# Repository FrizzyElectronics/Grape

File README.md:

# Grape

Grape es un Arduino&trade; compatible de fabricacion y diseño español. Destaca frente a otras placas por su rapidez de conexionado y por no necesitar el uso de protoboard para realizar los proyectos.

## Rasgos destacados

  - Conexion micro-USB
  - Corriente max de salida (5V) 2A
  - Pines de conexión rápida
  - Interruptor de encendido-apagado
  - 8 pines analogicos
  - Compatible con los shields de Arduino&trade; y con Arduino&trade; IDE

## Documentacion 

* **/Hardware** - Archivos de diseño en KiCad e Eagle, esquema en PDF
* **/Production** - Gerbers, BOM
* **/Design** - Logos, SVG 

Licencia
-------------------

Este producto es  **open source**! 

Por favor, revisa el archivo [LICENSE.md](https://github.com/FrizzyElectronics/Grape/blob/master/License.md) para más información. 

Si tiene alguna duda acerca del uso de esta licencia contatanos a traves de  info@frizzy.es

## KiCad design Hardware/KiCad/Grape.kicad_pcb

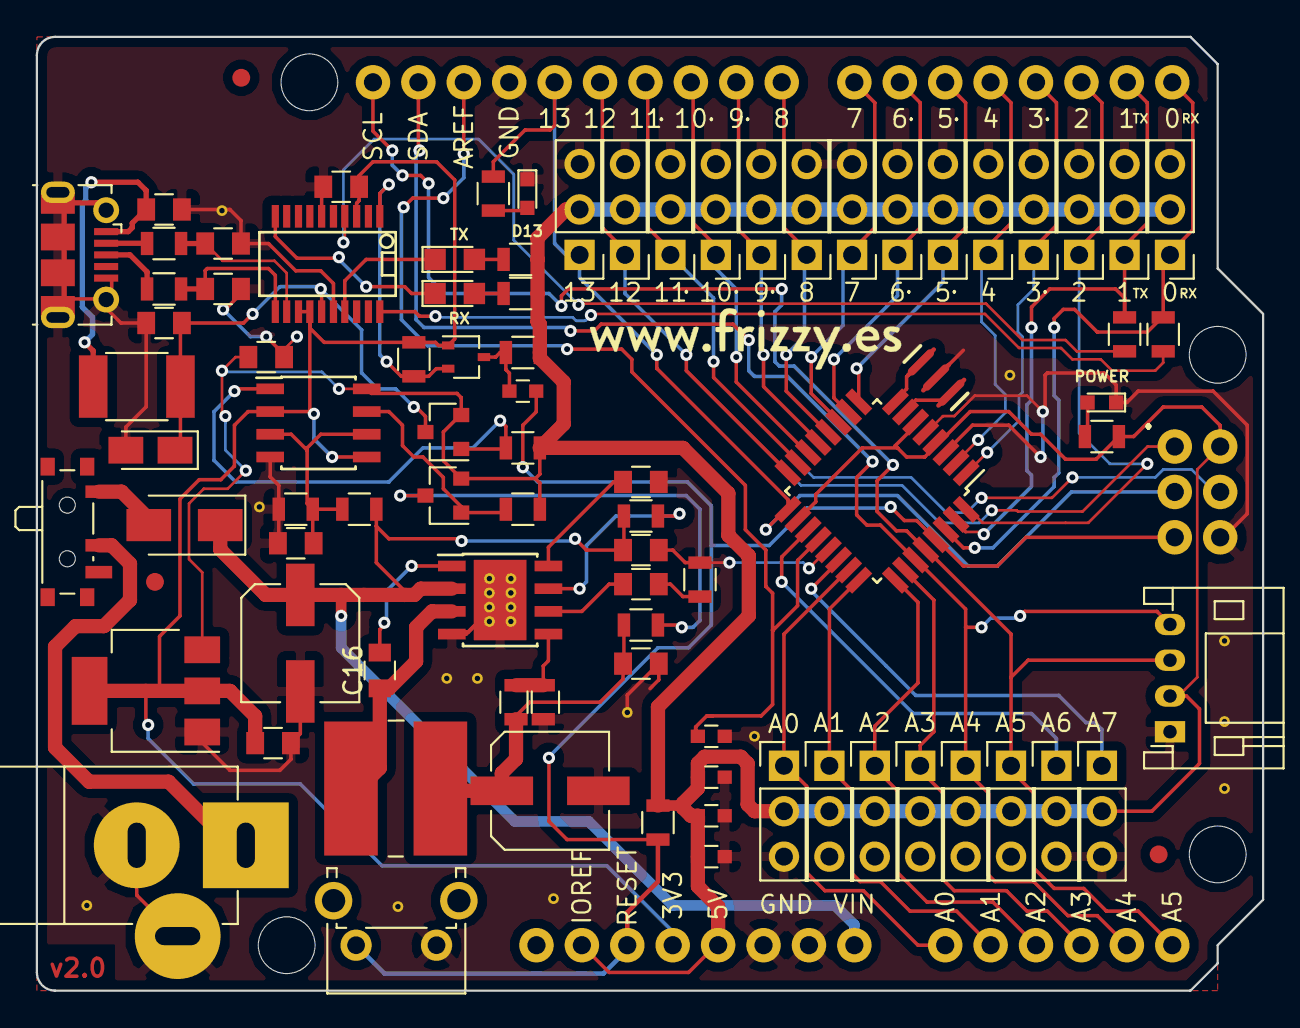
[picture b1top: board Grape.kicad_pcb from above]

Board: 2 copper layers, 68.6 x 53.3 mm, 85 parts (0 on the bottom side), 60 nets.

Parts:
C1, C2, C4, C10, C11, C15, C22, C23, C24: 100nF; C_0805
C3: 10nF; CP_Tantalum_Case-A_EIA-3216-18_Reflow
C5, C6, C13: 100nF; C_0603
C7, C9: 100uF; CP_Elec_6.3x5.3
C8: 3.3nF; C_0805
C12: 1uF; C_0603
C14: 10nF; C_0603
C16: 10nF; C_0805
C19, C20: 47pF; C_0805
D1: MBRA140; D_SMA
D2: YELLOW; LED_0603
D4: PURPLE; LED_0603
F2: 500mA; R_1812
J1: USB_MICROB; USB_Micro-B_Molex-105017-0001
J3: ARDUINO_R3
J19: POWER_JACKPTH; JACK_ALIM
L1: 10uH; L_Wuerth_WE-PD2-Typ-L
L2: 60R 100M Ferrite; L_0805
LED1: RED; LED_0805
LED2: GREEN; LED_0805
P1, P2, P3, P4, P5, P6, P7, P8, P9, P10, P11, P12, P13, P14, P15, P16, P17, P18, P19, P20, P21, P22: CONN_01X03; Pin_Header_Straight_1x03_Pitch2.54mm
P23: I2C; JST_PH_S4B-PH-K_04x2.00mm_Angled
Q1: 2N7002PW; SOT-323_SC-70
Q4, Q5: FDN340P; SOT-23
R1, R2, R4, R5, R6, R8: 1k; R_0805
R3, R14, R15, R16, R17, R18, R20: 10k; R_0805
R7: 5K6 1%; R_0805
R9: 6.8k; R_0805
R10: 1k 1%; R_0805
R11: 100k; R_0805
R12, R13: 27R; R_0805
S2: RESET; SW_Tactile_SPST_Angled_PTS645Vx39-2LFS
SW1: SW_SPDT; SW_SPDT_PCM12
U1: FT231XS; SSOP-20
U2: LM358; SOIC-8_3.9x4.9mm_Pitch1.27mm
U3: AMS1117-3.3; SOT-223
U4: ATMEGA328P_TQFP; TQFP-32_7x7mm_Pitch0.8mm
U8: MP2307SO; HTSOP-8-1EP_3.9x4.9mm_Pitch1.27mm_ThermalVias_LargeCopper
Y1: 16MHz; RESONATOR-SMD-3.2X1.3

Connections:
+3V3: C1.1, C24.1, J3.3.3V, Q1.1, R14.2, U1.3, U1.13, U1.14, U2.2, U2.5, U3.2, U3.4
+5V: C12.1, C13.1, C14.1, C23.1, J3.5V, J3.IORE, J3.VCC, P1.2, P2.2, P3.2, P4.2, P5.2, P6.2, P7.2, P8.2, P9.2, P10.2, P11.2, P12.2, P13.2, P14.2, P15.2, P16.2, P17.2, P18.2, P19.2, P20.2, P21.2, P22.2, P23.2, Q4.2, Q5.2, R1.2, R3.1, R4.2, R8.2, R15.2, R16.2, R20.2, U2.8, U3.3, U4.4, U4.6, U4.18
AD0: J3.A0, P4.1, U4.23
AD1: J3.A1, P9.1, U4.24
AD2: J3.A2, P14.1, U4.25
AD3: J3.A3, P18.1, U4.26
AD4/SDA: J3.A4, J3.SDA, P21.1, P23.4, U4.27
AD5/SCL: J3.A5, J3.SCL, P22.1, P23.3, U4.28
AD6: P10.1, U4.19
AD7: P5.1, U4.22
AREF: C5.1, J3.AREF, U4.20
DTR: C6.1, Q1.3, R15.1
GND: C1.2, C2.2, C3.2, C4.2, C5.2, C7.2, C9.2, C10.2, C11.2, C12.2, C13.2, C14.2, C15.2, C19.2, C20.2, C22.2, C23.2, C24.2, D2.1, D4.1, J1.5, J1.6, J3.GND@, J19.2, J19.3, P1.3, P2.3, P3.3, P4.3, P5.3, P6.3, P7.3, P8.3, P9.3, P10.3, P11.3, P12.3, P13.3, P14.3, P15.3, P16.3, P17.3, P18.3, P19.3, P20.3, P21.3, P22.3, P23.1, R9.2, R10.1, R17.1, S2.1, U1.6, U1.16, U2.4, U3.1, U4.3, U4.5, U4.21, U8.4, U8.9, Y1.2
IO2/PIN2: J3.D2, P11.1, U4.32
IO3/PIN3: J3.D3, P15.1, U4.1
IO4/PIN4: J3.D4, P19.1, U4.2
IO5/PIN5: J3.D5, P2.1, U4.9
IO6/PIN6: J3.D6, P7.1, U4.10
IO7/PIN7: J3.D7, P12.1, U4.11
IO8/PIN8: J3.D8, P16.1, U4.12
IO9/PIN9: J3.D9, P20.1, U4.13
MISO/PIN12: J3.D12, J3.MISO, P13.1, U4.16
MOSI/PIN11: J3.D11, J3.MOSI, P8.1, U4.15
unnamed: C4.1, F2.2, J1.1
unnamed: C8.1, U8.6
unnamed: C8.2, R9.1
unnamed: C11.1, U8.8
unnamed: C7.1, C15.1, L1.2, L2.1, R7.2
unnamed: C16.1, L1.1, U8.3
unnamed: C16.2, U8.1
unnamed: C19.1, R13.1, U1.11
unnamed: C20.1, R12.1, U1.12
unnamed: C22.1, R17.2, R18.1, U2.3, U2.6
unnamed: D1.2, SW1.1
unnamed: D2.2, R2.2
unnamed: D4.2, R8.1
unnamed: J1.2, R12.2
unnamed: J1.3, R13.2
unnamed: J19.1, SW1.2
unnamed: LED1.1, U1.17
unnamed: LED1.2, R4.1
unnamed: LED2.1, U1.10
unnamed: LED2.2, R1.1
unnamed: Q1.2, R14.1, U1.1
unnamed: Q4.1, R20.1, U2.1
unnamed: Q5.1, R16.1, U2.7
unnamed: R5.2, U1.20
unnamed: R6.2, U1.4
unnamed: R7.1, R10.2, U8.5
unnamed: R11.1, U8.7
unnamed: U4.7, Y1.1
unnamed: U4.8, Y1.3
RESET: C6.2, J3.RESE, R3.2, S2.2, U4.29
RX: J3.D0, P1.1, R5.1, U4.30
SCK/PIN13: J3.D13, J3.SCK, P17.1, R2.1, U4.17
SS/PIN10: J3.D10, P3.1, U4.14
TX: J3.D1, P6.1, R6.1, U4.31
USB_5V: C2.1, C3.1, F2.1, Q4.3, U1.15
VDD5: L2.2, Q5.3
VIN: C9.1, C10.1, D1.1, J3.VIN, R11.2, R18.2, U8.2

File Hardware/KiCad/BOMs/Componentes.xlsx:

Id | Identificador | Empaquetado | Cantidad | Identificación | Suministrador y ref
0 | C1,C2,C4,C10,C11,C15,C22,C23,C24 | C_0805 | 9 | 100nF
1 | C3 | CP_Tantalum_Case-A_EIA-3216-18_Reflow | 1 | 10nF
2 | C5,C6,C13 | C_0603 | 3 | 100nF
3 | C7,C9 | CP_Elec_6.3x5.3 | 2 | 100uF
4 | C8 | C_0805 | 1 | 3.3nF
5 | C12 | C_0603 | 1 | 1uF
6 | C14 | C_0603 | 1 | 10nF
7 | C16 | C_0805 | 1 | 10nF
8 | C19,C20 | C_0805 | 2 | 47pF
9 | D1 | D_SMA | 1 | MBRA140
10 | D2 | LED_0603 | 1 | YELLOW
11 | D4 | LED_0603 | 1 | PURPLE
12 | F2 | R_1812 | 1 | 500mA
13 | J19 | JACK_ALIM | 1 | POWER_JACKPTH
14 | L1 | L_Wurth_WE-PD2-Typ-L | 1 | 10uH
15 | L2 | L_0805 | 1 | 60R 100M Ferrite
16 | LED1 | LED_0805 | 1 | RED
17 | LED2 | LED_0805 | 1 | GREEN
18 | P1,P2,P3,P4,P5,P6,P7,P8,P9,P10,P11,P12,P13,P14,P15,P16,P17,P18,P19,P20,P21,P22 | Pin_Header_Straight_1x03_Pitch2.54mm | 22 | CONN_01X03
19 | P23 | JST_PH_S4B-PH-K_04x2.00mm_Angled | 1 | I2C
20 | Q1 | SOT-323_SC-70 | 1 | 2N7002PW
21 | Q4,Q5 | SOT-23 | 2 | FDN340P
22 | R1,R2,R4,R5,R6,R8 | R_0805 | 6 | 1k
23 | R3,R14,R15,R16,R17,R18,R20 | R_0805 | 7 | 10k
24 | R7 | R_0805 | 1 | 5K6 1%
25 | R9 | R_0805 | 1 | 6.8k
26 | R10 | R_0805 | 1 | 1k 1%
27 | R11 | R_0805 | 1 | 100k
28 | R12,R13 | R_0805 | 2 | 27R
29 | S2 | SW_Tactile_SPST_Angled_PTS645Vx39-2LFS | 1 | RESET
30 | SW1 | SW_SPDT_PCM12 | 1 | SW_SPDT
31 | U1 | SSOP-20 | 1 | FT231XS
32 | U2 | SOIC-8_3.9x4.9mm_Pitch1.27mm | 1 | LM358
33 | U3 | SOT-223 | 1 | AMS1117-3.3
34 | U4 | TQFP-32_7x7mm_Pitch0.8mm | 1 | ATMEGA328P_TQFP
35 | U8 | HTSOP-8-1EP_3.9x4.9mm_Pitch1.27mm_ThermalVias_LargeCopper | 1 | MP2307SO
36 | Y1 | RESONATOR-SMD-3.2X1.3 | 1 | 16MHz
37 | J1 | USB_Micro-B_Molex-105017-0001 | 1 | USB_MICROB

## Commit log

2016-08-02 Add files via upload
    Version 1.0
2016-11-19 Ultima version mandada a fabrica
2017-01-09 Vias Tapadas, USB cambiado, TX RX añadido
    se ha reparado tambien la alimentacion de 5V
2017-07-17 Ficheros de diseño añadidos
2017-07-17 Limpieza de archivos basura
2017-07-17 Iniciando la documentacion
2017-07-17 Readme añadido
2017-07-17 License added
2017-07-17 Svg añadido al readme
2018-01-14 Comenzando la migracion a kicad, esquema y hojas creadas
2018-01-14 Primera pagina terminada
2018-01-14 Microcontrolador añadido
2018-01-14 Alimentacion comenzada
2018-01-15 Alimentacion terminada
2018-01-15 Esquema terminado y ERC pasado
2018-01-15 cvpcb terminado
2018-01-15 Semiconductores colocados en placa y 3D añadido
2018-01-17 3D terminado
2018-01-17 Comenzado el enrutado
2018-01-25 copia de seguridad
2018-01-29 Enrutando la placa
2018-01-29 enrutado completo
2018-01-29 empezando con la serigrafia
2018-01-30 Avanzando con la serigrafia
2018-02-04 Serigrafia web añadida
2018-02-04 Usb cambiado
2018-02-04 Terminada
2018-04-22 Actualizado .gitignore y creado archivo .pro
2018-05-06 Cambiando el árbol de carpetas
2018-05-06 Carpeta limpada de .mod's
2018-05-06 3D enlazado y arbol de carpetas terminado
2018-05-13 Valores cambiados
2018-06-08 Añadida serigrafia en PWM pins
2018-06-08 Gerbers generados y mandado a fabrica para prueba
    Fabricado con JLCPCB a 1.2mm y sin merge
2018-07-14 Re-rellenado el plano de masa
2018-07-15 Gerbers exportados
2020-11-14 preparando archivos
2020-11-14 Prueba de guardado
2020-11-14 Conector y CH340C implementado
2020-11-14 Esquema terminado
    Falta comprobar
